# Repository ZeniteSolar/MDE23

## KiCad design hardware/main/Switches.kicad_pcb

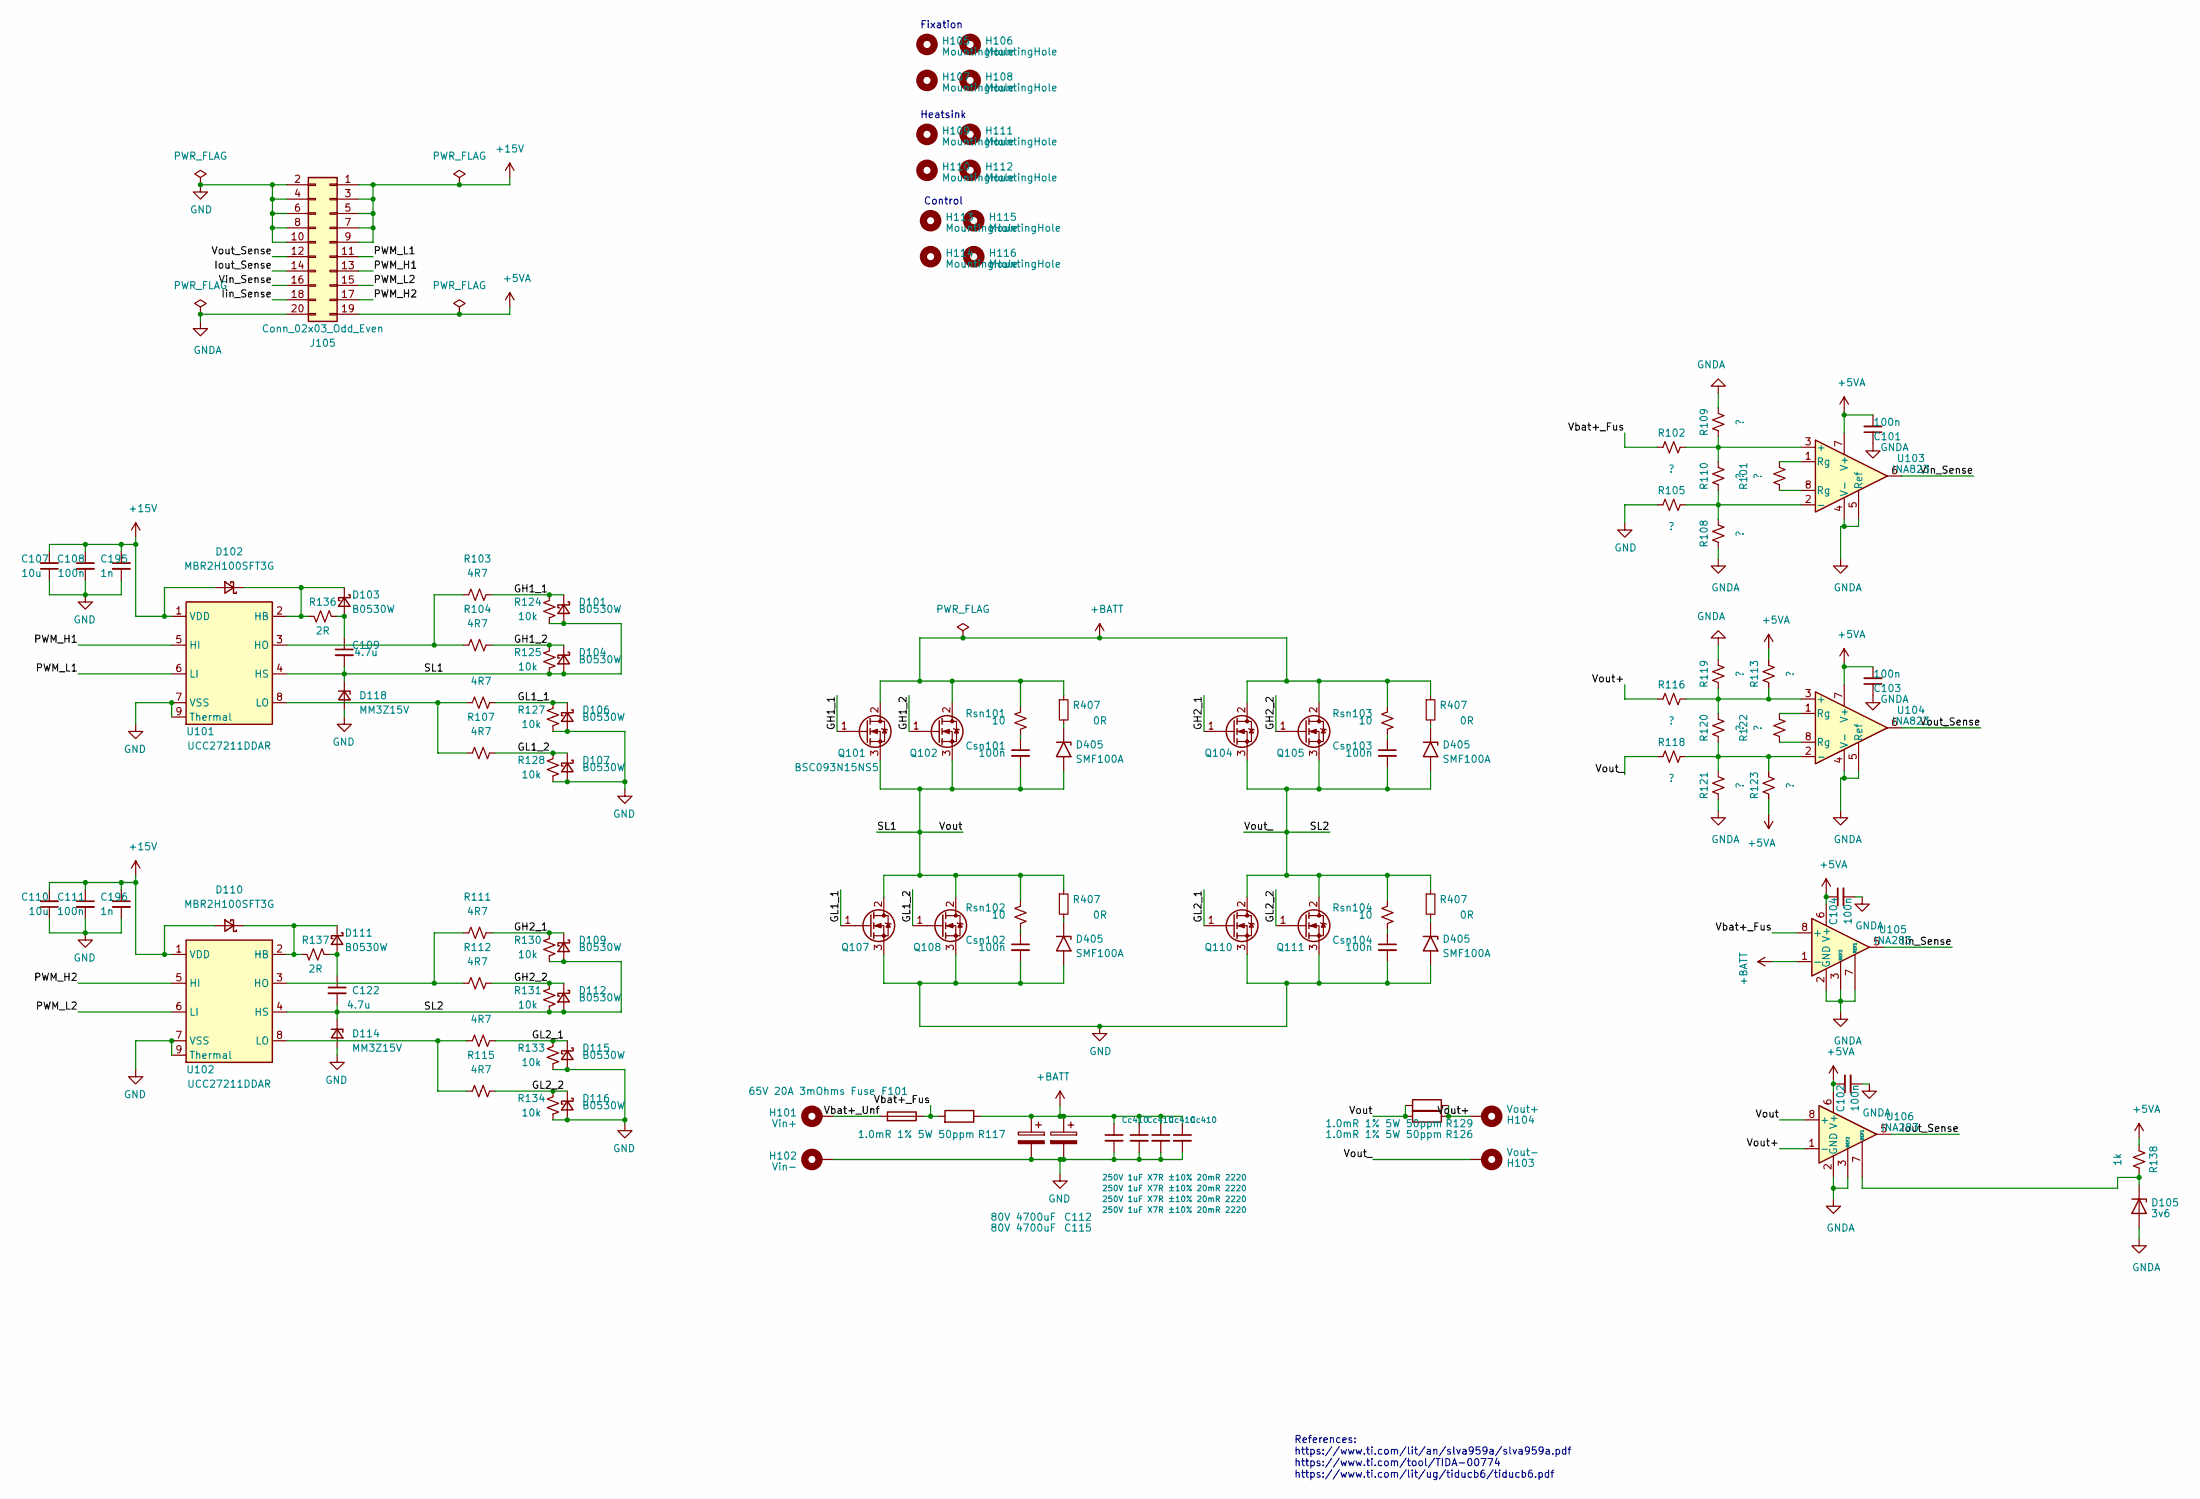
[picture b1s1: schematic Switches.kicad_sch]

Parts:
C101, C102, C103, C104, C108, C111: 100n; C_0805_2012Metric_Pad1.18x1.45mm_HandSolder
C107, C110: 10u; C_1210_3225Metric_Pad1.33x2.70mm_HandSolder
C109, C122: 4.7u; C_1210_3225Metric_Pad1.33x2.70mm_HandSolder
C112, C115: 80V 4700uF; CP_Radial_D12.5mm_P5.00mm
C195, C196: 1n; C_0603_1608Metric_Pad1.08x0.95mm_HandSolder
Cc410: 250V 1uF X7R ±10% 20mR 2220; C_2220_5650Metric
Csn101, Csn102, Csn103, Csn104: 100n; R_1206_3216Metric
D101, D103, D104, D106, D107, D109, D111, D112, D115, D116: B0530W; D_SOD-123F
D102, D110: MBR2H100SFT3G; D_SOD-123F
D105: 3v6; D_MiniMELF
D114, D118: MM3Z15V; D_SOD-323
D405: SMF100A; D_SOD-123F
F101: 65V 20A 3mOhms Fuse; S6125-F
H101: Vin+; MountingHole_13mmx13mm_Rectangular
H102: Vin-; MountingHole_13mmx13mm_Rectangular
H103: Vout-; MountingHole_13mmx13mm_Rectangular
H104: Vout+; MountingHole_13mmx13mm_Rectangular
H105, H106, H107, H108, H109, H110, H111, H112, H113, H114, H115, H116: MountingHole; MountingHole_3.5mm_Pad
J105: Conn_02x03_Odd_Even; PinHeader_2x10_P1.27mm_Vertical_SMD
Q101, Q102, Q104, Q105, Q107, Q108, Q110, Q111: BSC093N15NS5; TDSON-8-3
R101, R102, R105, R108, R109, R110, R113, R116, R118, R119, R120, R121, R122, R123: ?; R_0805_2012Metric_Pad1.20x1.40mm_HandSolder
R103, R104, R106, R107, R111, R112, R114, R115: 4R7; R_0805_2012Metric_Pad1.20x1.40mm_HandSolder
R117, R126, R129: 1.0mR 1% 5W 50ppm; R_2512_6332Metric_Pad1.40x3.35mm_HandSolder
R124, R125, R127, R128, R130, R131, R133, R134: 10k; R_0603_1608Metric_Pad0.98x0.95mm_HandSolder
R136, R137: 2R; R_0603_1608Metric_Pad0.98x0.95mm_HandSolder
R138: 1k; R_0805_2012Metric_Pad1.20x1.40mm_HandSolder
R407: 0R; R_0805_2012Metric_Pad1.20x1.40mm_HandSolder
Rsn101, Rsn102, Rsn103, Rsn104: 10; R_1206_3216Metric
U101, U102: UCC27211DDAR; SOIC-8-1EP_3.9x4.9mm_P1.27mm_EP2.514x3.2mm
U103, U104: INA823; SOIC-8_3.9x4.9mm_P1.27mm
U105, U106: INA283; SOIC-8_3.9x4.9mm_P1.27mm

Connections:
+5VA: C101.2, C102.1, C103.2, C104.1, J105.19, R113.2, R123.1, R138.1, U103.7 (V+), U104.7 (V+), U105.6 (V+), U106.6 (V+)
+15V: C107.2, C108.1, C110.2, C111.1, C195.1, C196.1, D102.2 (A), D110.2 (A), J105.1, J105.3, J105.5, J105.7, J105.9, U101.1 (VDD), U102.1 (VDD)
+BATT: C112.1, C115.1, Q101.2 (D), Q102.2 (D), Q104.2 (D), Q105.2 (D), R117.1, Rsn101.1, Rsn103.1, U105.1 (-); also elsewhere on the board
/GH1_1: D101.1 (K), Q101.1 (G), R103.1, R124.2
/GH1_2: D104.1 (K), Q102.1 (G), R104.1, R125.2
/GH2_1: D109.1 (K), Q104.1 (G), R111.1, R130.2
/GH2_2: D112.1 (K), Q105.1 (G), R112.1, R131.2
/GL1_1: D106.1 (K), Q107.1 (G), R106.1, R127.2
/GL1_2: D107.1 (K), Q108.1 (G), R107.1, R128.2
/GL2_1: D115.1 (K), Q110.1 (G), R114.1, R133.2
/GL2_2: D116.1 (K), Q111.1 (G), R115.1, R134.2
/Iin_Sense: J105.18, U105.5
/Iout_Sense: J105.14, U106.5
/PWM_H1: J105.13, U101.5 (HI)
/PWM_H2: J105.17, U102.5 (HI)
/PWM_L1: J105.11, U101.6 (LI)
/PWM_L2: J105.15, U102.6 (LI)
/SL1: C109.2, Csn101.2, D101.2 (A), D104.2 (A), D118.1 (K), Q101.3 (S), Q102.3 (S), Q107.2 (D), Q108.2 (D), R124.1, R125.1, R126.2, R129.2, Rsn102.1, U101.4 (HS), U106.8 (+); also elsewhere on the board
/SL2: C122.2, Csn103.2, D109.2 (A), D112.2 (A), D114.1 (K), H103.1, Q104.3 (S), Q105.3 (S), Q110.2 (D), Q111.2 (D), R118.1, R130.1, R131.1, Rsn104.1, U102.4 (HS); also elsewhere on the board
/Vbat+_Fus: F101.1, R102.1, R117.2, U105.8 (+)
/Vbat+_Unf: F101.2, H101.1
/Vin_Sense: J105.16, U103.6
/Vout+: H104.1, R116.1, R126.1, R129.1, U106.1 (-)
/Vout_Sense: J105.12, U104.6
GND: C107.1, C108.2, C110.1, C111.2, C112.2, C115.2, C195.2, C196.2, Csn102.2, Csn104.2, D106.2 (A), D107.2 (A), D114.2 (A), D115.2 (A), D116.2 (A), D118.2 (A), H102.1, J105.2, J105.4, J105.6, J105.8, J105.10, Q107.3 (S), Q108.3 (S), Q110.3 (S), Q111.3 (S), R105.1, R127.1, R128.1, R133.1, R134.1, U101.7 (VSS), U101.9 (Thermal), U102.7 (VSS), U102.9 (Thermal); also elsewhere on the board
GNDA: C101.1, C102.2, C103.1, C104.2, D105.2 (A), J105.20, R108.1, R109.2, R119.2, R121.1, U103.4 (V-), U103.5 (Ref), U104.4 (V-), U104.5 (Ref), U105.2 (GND), U105.3 (REF2), U105.7 (REF1), U106.2 (GND), U106.3 (REF2)
unnamed: Csn101.1, Rsn101.2
unnamed: Csn102.1, Rsn102.2
unnamed: Csn103.1, Rsn103.2
unnamed: Csn104.1, Rsn104.2
unnamed: D102.1 (K), D103.1 (K), R136.1, U101.2 (HB)
unnamed: C109.1, D103.2 (A), R136.2
unnamed: D105.1 (K), R138.2, U106.7 (REF1)
unnamed: D110.1 (K), D111.1 (K), R137.1, U102.2 (HB)
unnamed: C122.1, D111.2 (A), R137.2
unnamed: R101.1, U103.1 (Rg)
unnamed: R101.2, U103.8 (Rg)
unnamed: R122.1, U104.1 (Rg)
unnamed: R122.2, U104.8 (Rg)
unnamed: R103.2, R104.2, U101.3 (HO)
unnamed: R106.2, R107.2, U101.8 (LO)
unnamed: R111.2, R112.2, U102.3 (HO)
unnamed: R114.2, R115.2, U102.8 (LO)
unnamed: R102.2, R109.1, R110.2, U103.3 (+)
unnamed: R105.2, R108.2, R110.1, U103.2 (-)
unnamed: R113.1, R116.2, R119.1, R120.2, U104.3 (+)
unnamed: R118.2, R120.1, R121.2, R123.2, U104.2 (-)

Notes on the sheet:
Control
References: https://www.ti.com/lit/an/slva959a/slva959a.pdf https://www.ti.com/tool/TIDA-00774 https://www.ti.com/lit/ug/tiducb6/tiducb6.pdf
Heatsink
Fixation

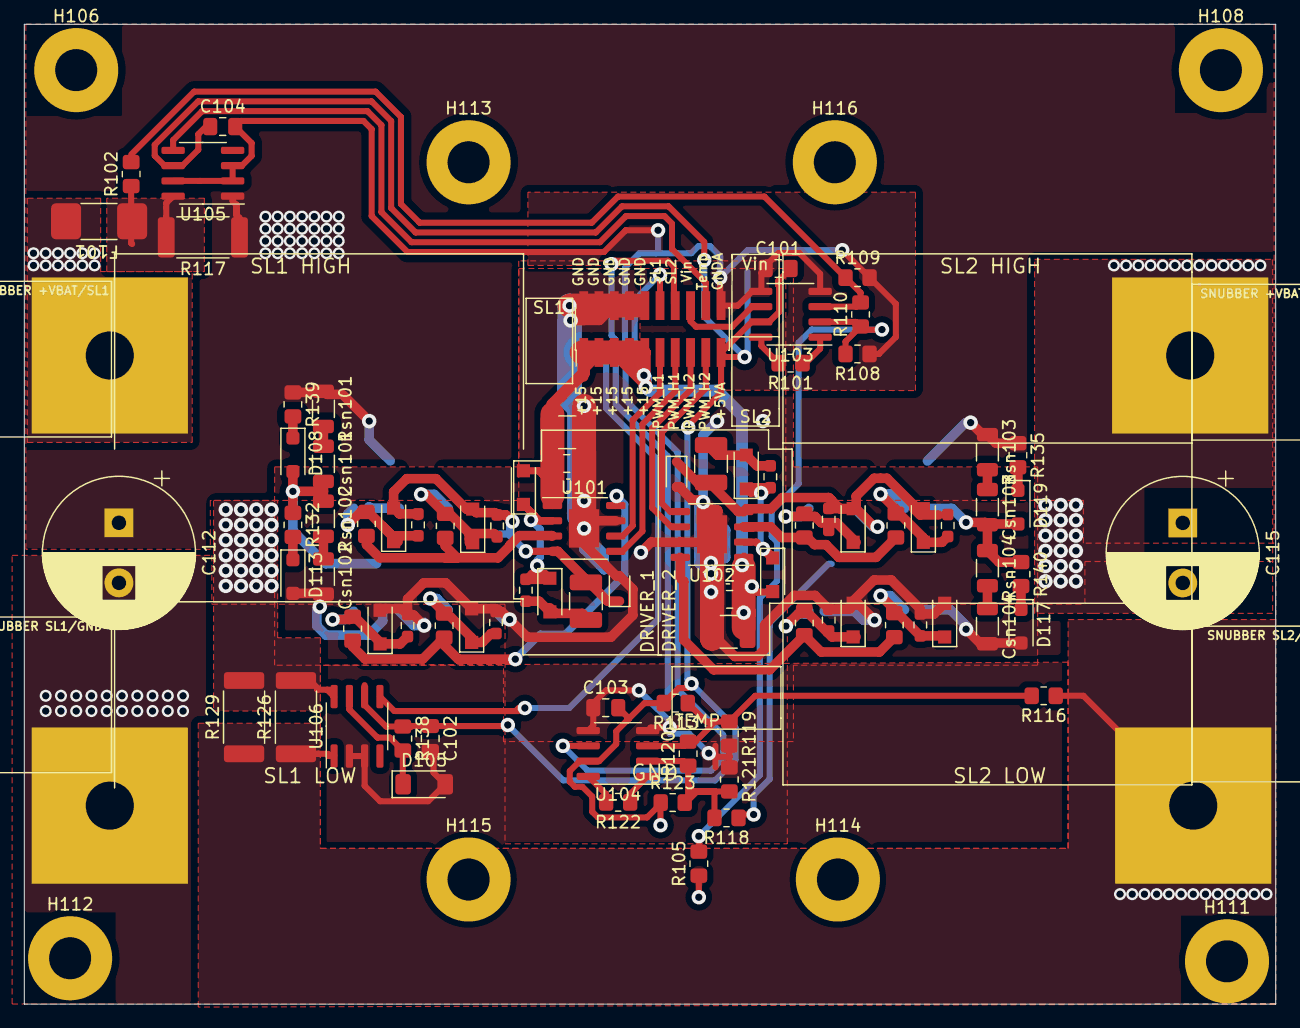
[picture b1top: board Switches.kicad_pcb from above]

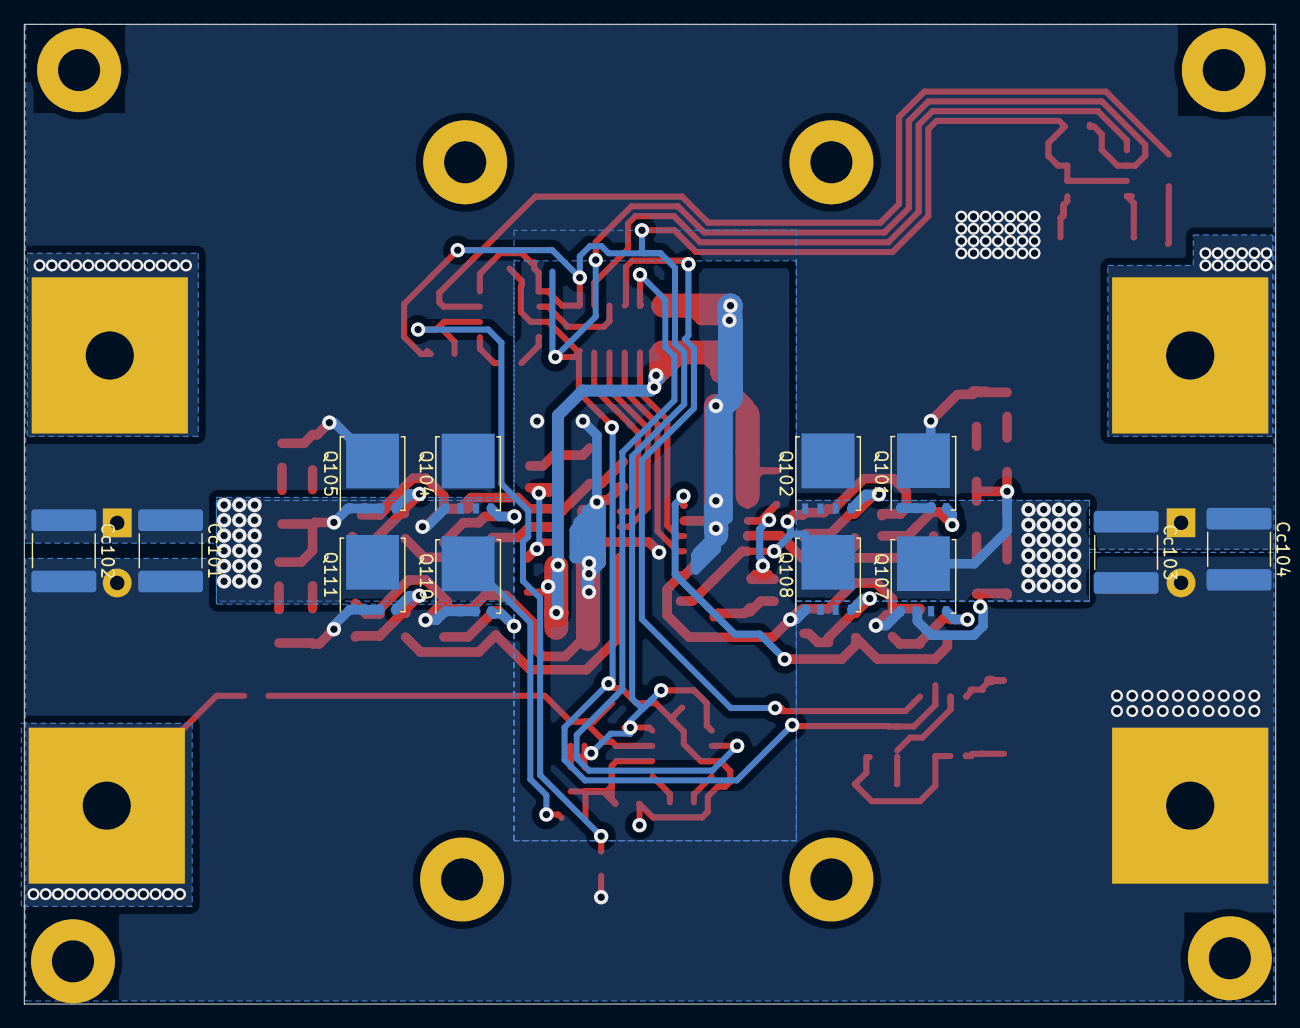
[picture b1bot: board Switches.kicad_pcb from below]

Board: 2 copper layers, 104.1 x 81.5 mm, 113 parts (12 on the bottom side), 51 nets.

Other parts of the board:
Cc101, Cc102, Cc103, Cc104: 250V 1uF X7R ±10% 20mR 2220; C_2220_5650Metric
D108, D113, D117, D119: SMF100A; D_SOD-123F
R132, R135, R139, R140: 0R; R_0805_2012Metric_Pad1.20x1.40mm_HandSolder

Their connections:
+BATT: Cc101.1, Cc102.1, Cc103.1, Cc104.1, R135.1, R139.1; also elsewhere on the board
/SL1: D108.2 (A2), R132.1; also elsewhere on the board
/SL2: D119.2 (A2), R140.1; also elsewhere on the board
GND: Cc101.2, Cc102.2, Cc103.2, Cc104.2, D113.2 (A2), D117.2 (A2); also elsewhere on the board
unnamed: D108.1 (A1), R139.2
unnamed: D113.1 (A1), R132.2
unnamed: D117.1 (A1), R140.2
unnamed: D119.1 (A1), R135.2

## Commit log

2023-03-30 Added MDE23 schematic derived of MAM21
2023-04-01 board finalized
2023-04-04 Update gitignore
2023-04-04 Finalize board sended to faaabrication
2023-04-14 add interactive BOM
